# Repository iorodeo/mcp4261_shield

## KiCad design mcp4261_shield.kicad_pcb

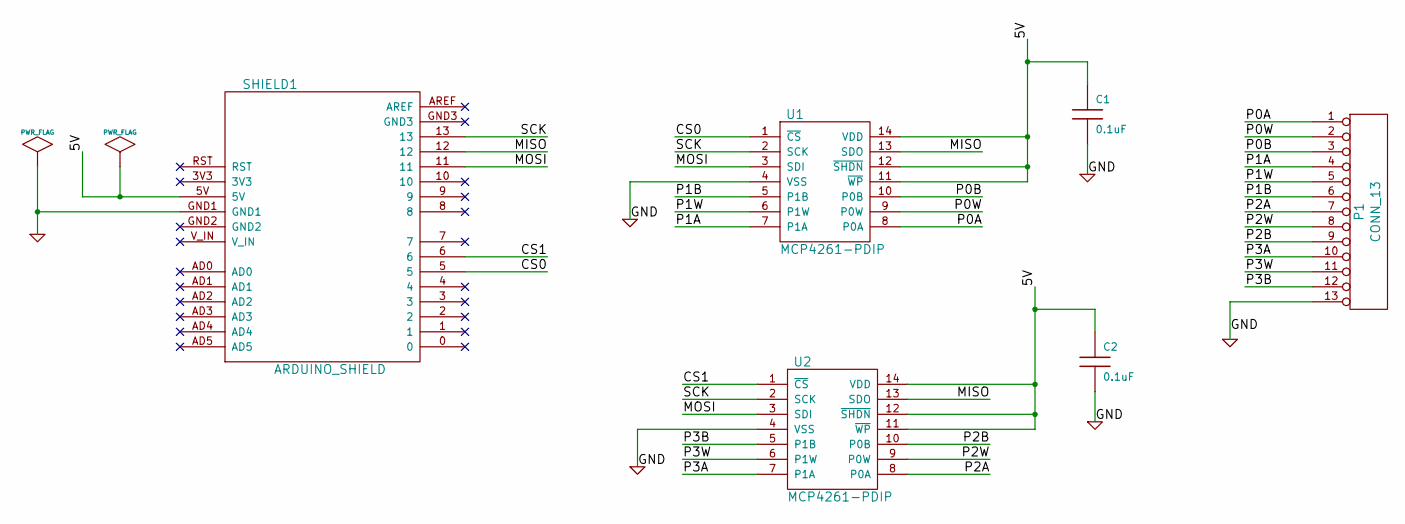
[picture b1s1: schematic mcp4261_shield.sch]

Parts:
C1, C2: 0.1uF
P1: CONN_13
SHIELD1: ARDUINO_SHIELD
U1, U2: MCP4261-PDIP

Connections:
/5V: C1.1, C2.1, SHIELD1.5V, U1.11 (~WP), U1.12 (~SHDN), U1.14 (VDD), U2.11 (~WP), U2.12 (~SHDN), U2.14 (VDD)
/CS0: SHIELD1.5, U1.1 (~CS)
/CS1: SHIELD1.6, U2.1 (~CS)
/MISO: SHIELD1.12, U1.13 (SDO), U2.13 (SDO)
/MOSI: SHIELD1.11, U1.3 (SDI), U2.3 (SDI)
/P0A: P1.1, U1.8 (P0A)
/P0B: P1.3, U1.10 (P0B)
/P0W: P1.2, U1.9 (P0W)
/P1A: P1.4, U1.7 (P1A)
/P1B: P1.6, U1.5 (P1B)
/P1W: P1.5, U1.6 (P1W)
/P2A: P1.7, U2.8 (P0A)
/P2B: P1.9, U2.10 (P0B)
/P2W: P1.8, U2.9 (P0W)
/P3A: P1.10, U2.7 (P1A)
/P3B: P1.12, U2.5 (P1B)
/P3W: P1.11, U2.6 (P1W)
/SCK: SHIELD1.13, U1.2 (SCK), U2.2 (SCK)
GND: C1.2, C2.2, P1.13, SHIELD1.GND1, U1.4 (VSS), U2.4 (VSS)

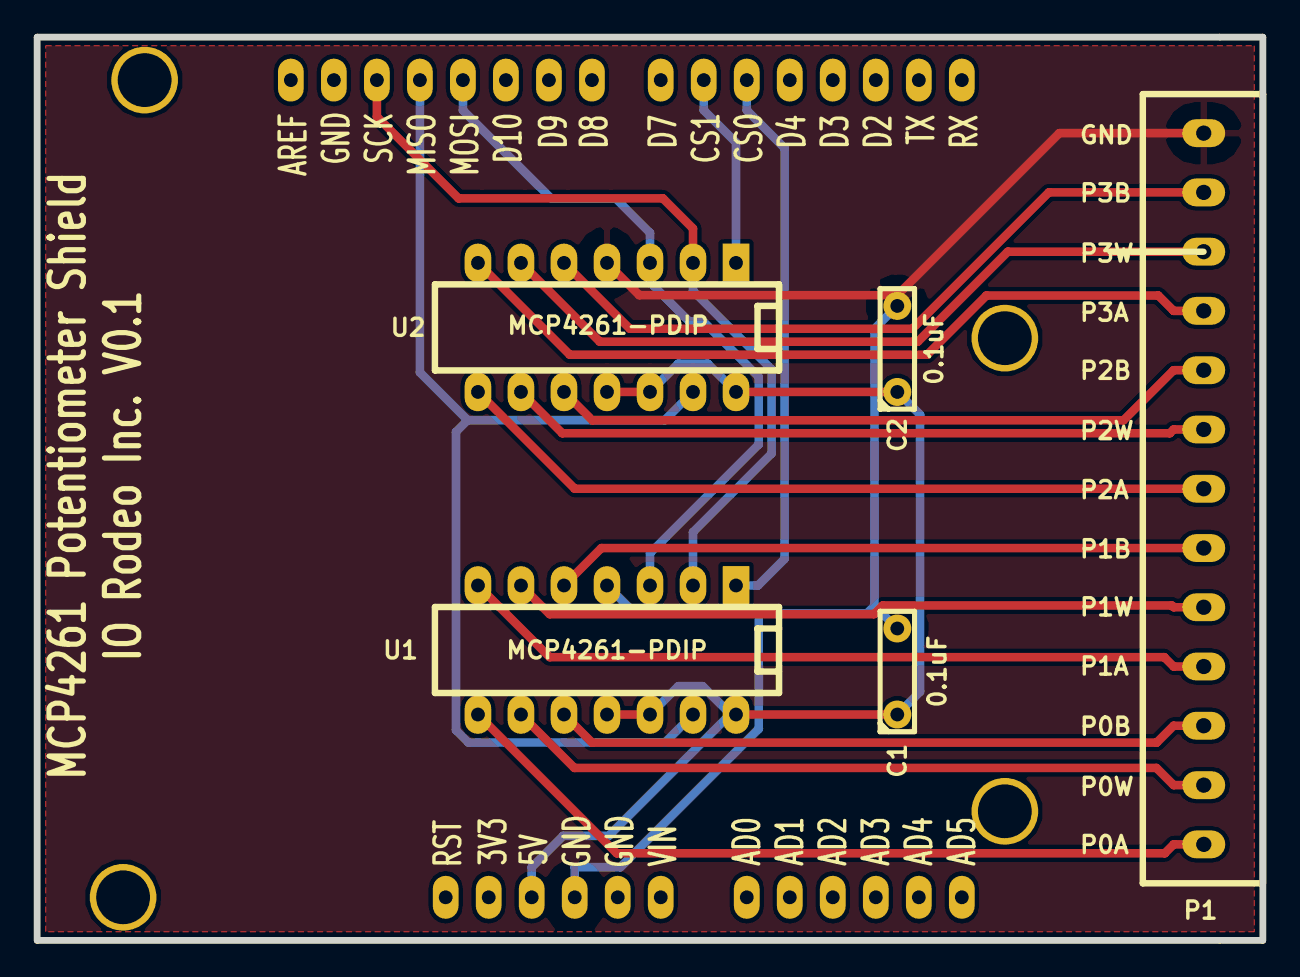
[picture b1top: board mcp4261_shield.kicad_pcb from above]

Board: 2 copper layers, 72.4 x 53.3 mm, 6 parts (0 on the bottom side), 19 nets.

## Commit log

2012-09-24 Project creation.
2013-08-25 Re-worked layout - finialize initial v0.1 design.
2013-12-27 Added bill of materials.
2014-04-10 Added svg and pdf of schematic.
2021-01-07 Changed arduino libs address on schematic.
